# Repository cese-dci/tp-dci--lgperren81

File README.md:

# tp-dci--lgperren81
tp-dci--lgperren81 created by GitHub Classroom
Carpeta que contiene el TP Final de la materia "Diseño de Circuitos Impresos".
CESE 9° Cohorte - 2019

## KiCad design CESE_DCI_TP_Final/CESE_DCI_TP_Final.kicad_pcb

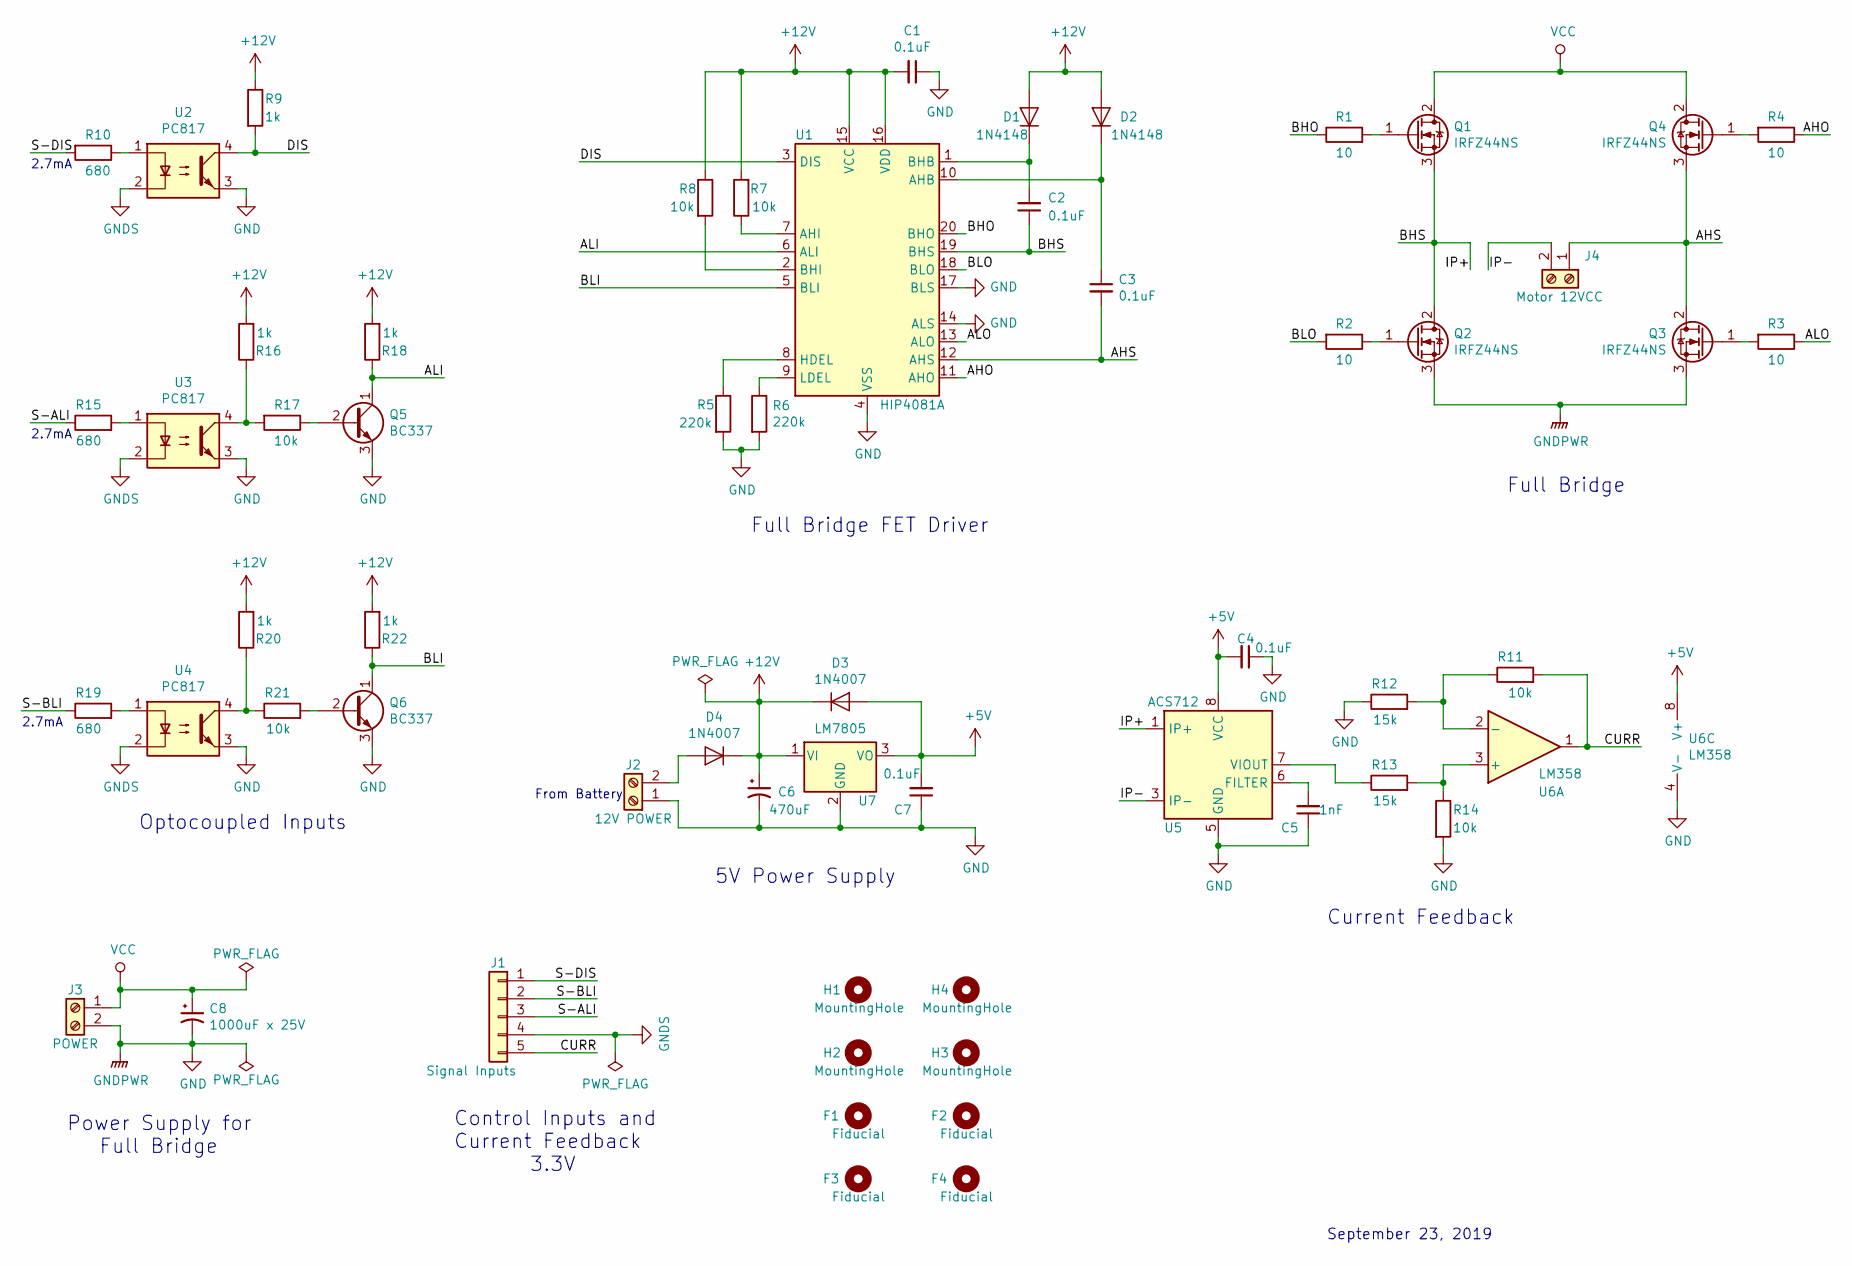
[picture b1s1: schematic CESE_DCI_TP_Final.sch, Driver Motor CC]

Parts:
C1, C2, C3, C4, C7: 0.1uF; C_1206_3216Metric_Pad1.42x1.75mm_HandSolder; Digi-Key Number 399-7357-2-ND
C5: 1nF; C_1206_3216Metric_Pad1.42x1.75mm_HandSolder; Digi-Key Number 399-17173-2-ND
C6: 470uF; CP_Radial_D10.0mm_P5.00mm; Digi-Key Number P10386TB-ND
C8: 1000uF x 25V; CP_Radial_D16.0mm_P7.50mm; Digi-Key Number 493-14604-3-ND
D1, D2: 1N4148; D_DO-35_SOD27_P7.62mm_Horizontal; Digi-Key Number 1N4148FS-ND
D3, D4: 1N4007; D_DO-41_SOD81_P10.16mm_Horizontal; Digi-Key Number 1N4007FSCT-ND
F1, F2, F3, F4: Fiducial; Fiducial_0.5mm_Dia_1mm_Outer
H1, H2, H3, H4: MountingHole; MountingHole_2.7mm_M2.5
J1: Signal Inputs; PinHeader_1x05_P2.54mm_Vertical; Digi-Key Number 732-5318-ND
J2: 12V POWER; TerminalBlock_bornier-2_P5.08mm; Digi-Key Number A113320-ND
J3: POWER; TerminalBlock_bornier-2_P5.08mm; Digi-Key Number A113320-ND
J4: Motor 12VCC; TerminalBlock_bornier-2_P5.08mm; Digi-Key Number A113320-ND
Q1, Q2, Q3, Q4: IRFZ44NS; TO-263-2; Digi-Key Number IRFZ44NSTRLPBFTR-ND
Q5, Q6: BC337; TO-92_Inline; Digi-Key Number BC33725TFRTR-ND
R1, R2, R3, R4: 10; R_1206_3216Metric_Pad1.42x1.75mm_HandSolder; Digi-Key Number CRM1206-FX-10R0ELFCT-ND
R5, R6: 220k; R_1206_3216Metric_Pad1.42x1.75mm_HandSolder; Digi-Key Number A130566TR-ND
R7, R8, R11, R14, R17, R21: 10k; R_1206_3216Metric_Pad1.42x1.75mm_HandSolder; Digi-Key Number 311-10KERTR-ND
R9, R16, R20, R22: 1k; R_1206_3216Metric_Pad1.42x1.75mm_HandSolder; Digi-Key Number CR1206-JW-102ELFTR-ND
R10, R15, R19: 680; R_1206_3216Metric_Pad1.42x1.75mm_HandSolder; Digi-Key Number 311-680FRCT-ND
R12, R13: 15k; R_1206_3216Metric_Pad1.42x1.75mm_HandSolder; Digi-Key Number A129824TR-ND
R18: 1k; R_1206_3216Metric_Pad1.42x1.75mm_HandSolder
U1: HIP4081A; DIP-20_W7.62mm_Socket; Digi-Key Number HIP4081AIPZ-ND
U2, U3, U4: PC817; DIP-4_W7.62mm; Digi-Key Number EL817-ND
U5: ACS712; SOIC-8_3.9x4.9mm_P1.27mm; Digi-Key Number 620-1190-2-ND
U6: LM358; SOIC-8-1EP_3.9x4.9mm_P1.27mm_EP2.35x2.35mm; Digi-Key Number 497-1591-2-ND
U7: LM7805; TO-220-3_Vertical; Digi-Key Number 296-47192-ND

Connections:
+5V: C4.2, C7.2, D3.2 (A), U5.8 (VCC), U6.8 (V+), U7.3 (VO)
+12V: C1.2, C6.1, D1.2 (A), D2.2 (A), D3.1 (K), D4.1 (K), R7.2, R8.1, R9.1, R16.2, R18.2, R20.2, R22.2, U1.15 (VCC), U1.16 (VDD), U7.1 (VI)
/AHO: R4.1, U1.11 (AHO)
/AHS: C3.2, J4.1, Q3.2 (D), Q4.3 (S), U1.12 (AHS)
/ALI: Q5.1 (C), R18.1, U1.6 (ALI)
/ALO: R3.1, U1.13 (ALO)
/BHO: R1.1, U1.20 (BHO)
/BHS: C2.1, Q1.3 (S), Q2.2 (D), U1.19 (BHS), U5.1 (IP+), U5.2 (IP+)
/BLI: Q6.1 (C), R22.1, U1.5 (BLI)
/BLO: R2.2, U1.18 (BLO)
/CURR: J1.5, R11.2, U6.1
/DIS: R9.2, U1.3 (DIS), U2.4
/IP-: J4.2, U5.3 (IP-), U5.4 (IP-)
/S-ALI: J1.3, R15.1
/S-BLI: J1.2, R19.1
/S-DIS: J1.1, R10.2
GND: C1.1, C4.1, C5.1, C6.2, C7.1, C8.2, J2.1, J3.2, Q2.3 (S), Q3.3 (S), Q5.3 (E), Q6.3 (E), R5.2, R6.2, R12.1, R14.2, U1.4 (VSS), U1.14 (ALS), U1.17 (BLS), U2.3, U3.3, U4.3, U5.5 (GND), U6.4 (V-), U7.2 (GND)
GNDS: J1.4, U2.2, U3.2, U4.2
unnamed: C2.2, D1.1 (K), U1.1 (BHB)
unnamed: C3.1, D2.1 (K), U1.10 (AHB)
unnamed: C5.2, U5.6 (FILTER)
unnamed: D4.2 (A), J2.2
unnamed: Q1.1 (G), R1.2
unnamed: Q2.1 (G), R2.1
unnamed: Q3.1 (G), R3.2
unnamed: Q4.1 (G), R4.2
unnamed: Q5.2 (B), R17.1
unnamed: Q6.2 (B), R21.2
unnamed: R5.1, U1.8 (HDEL)
unnamed: R6.1, U1.9 (LDEL)
unnamed: R7.1, U1.7 (AHI)
unnamed: R8.2, U1.2 (BHI)
unnamed: R10.1, U2.1
unnamed: R11.1, R12.2, U6.2 (-)
unnamed: R13.1, U5.7 (VIOUT)
unnamed: R13.2, R14.1, U6.3 (+)
unnamed: R15.2, U3.1
unnamed: R16.1, R17.2, U3.4
unnamed: R19.2, U4.1
unnamed: R20.1, R21.1, U4.4
VCC: C8.1, J3.1, Q1.2 (D), Q4.2 (D)

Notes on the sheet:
Control Inputs and Current Feedback 3.3V
From Battery
2.7mA
September 23, 2019
Current Feedback
Full Bridge
Full Bridge FET Driver
5V Power Supply
Optocoupled Inputs
Power Supply for Full Bridge

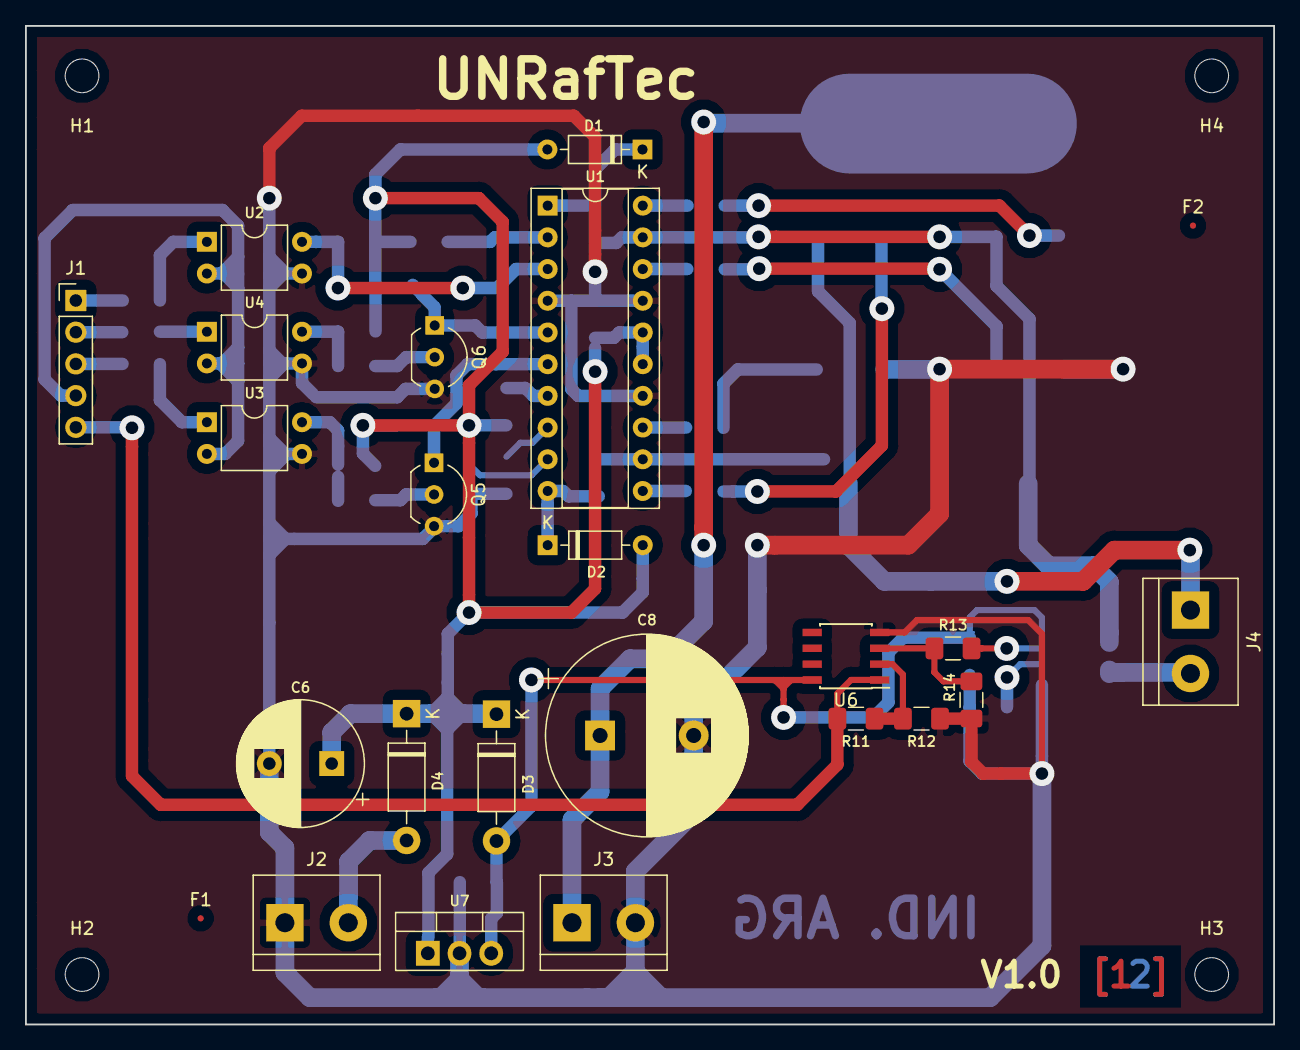
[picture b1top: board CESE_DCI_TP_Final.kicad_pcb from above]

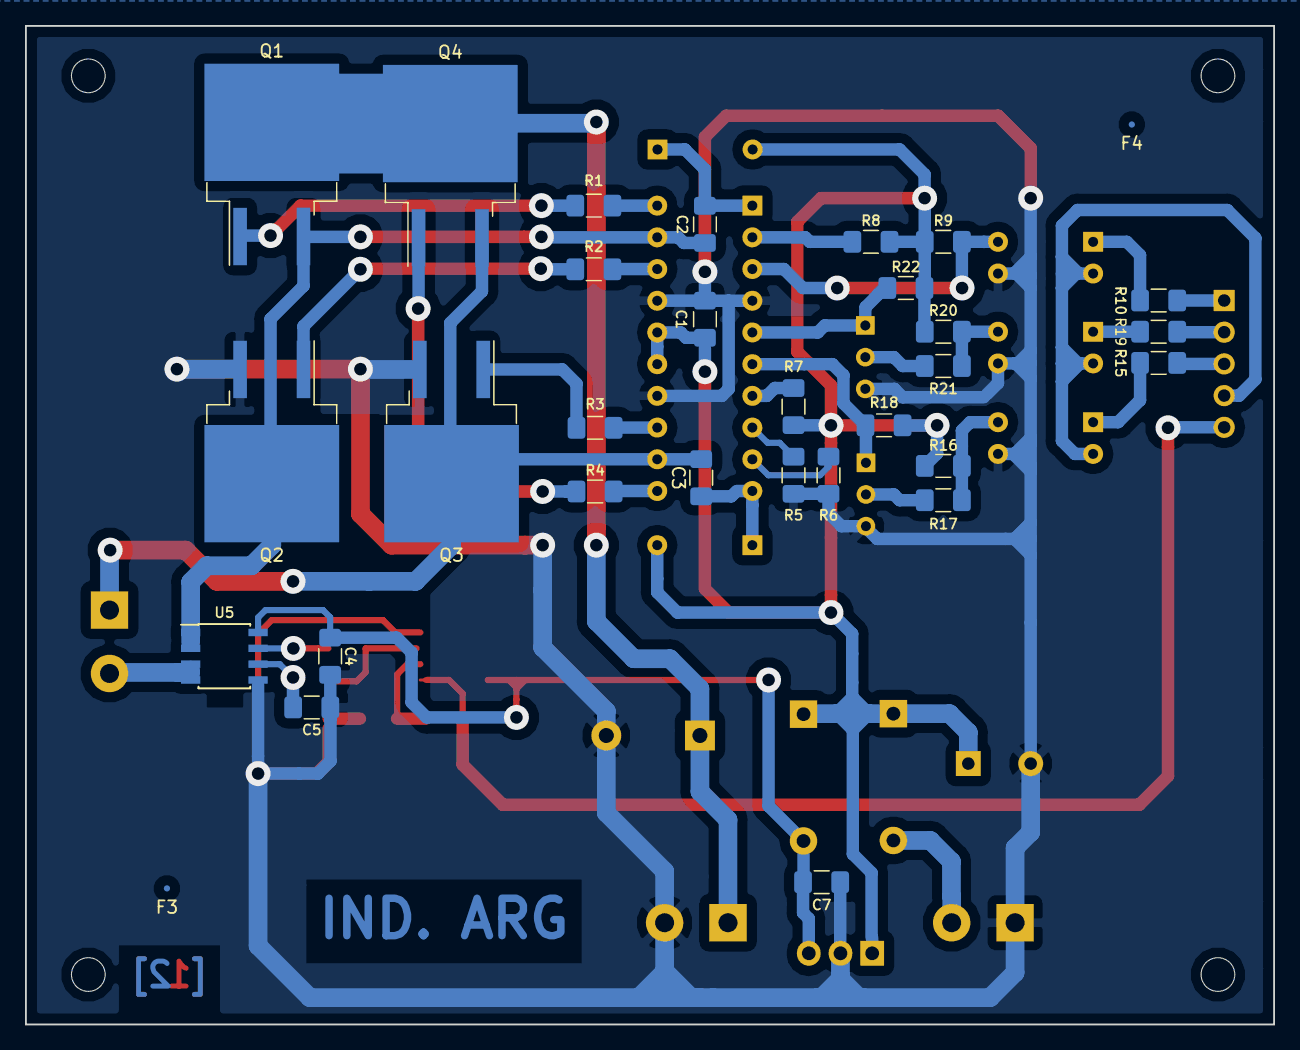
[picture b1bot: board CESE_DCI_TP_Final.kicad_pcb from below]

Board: 2 copper layers, 100.0 x 80.0 mm, 59 parts (31 on the bottom side), 41 nets.

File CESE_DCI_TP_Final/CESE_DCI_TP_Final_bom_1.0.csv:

Component,Description,Part,References,Value,Footprint,Quantity Per PCB,Datasheet
1,"Unpolarized capacitor, small symbol",C_Small,C1 C2 C3 C4 C7,0.1uF,C_1206_3216Metric_Pad1.42x1.75mm_HandSolder,5,~
2,"Polarized capacitor, small US symbol",CP1_Small,C8,1000uF x 25V,CP_Radial_D16.0mm_P7.50mm,1,~
3,"Unpolarized capacitor, small symbol",C_Small,C5,1nF,C_1206_3216Metric_Pad1.42x1.75mm_HandSolder,1,~
4,"Polarized capacitor, small US symbol",CP1_Small,C6,470uF,CP_Radial_D10.0mm_P5.00mm,1,~
5,"1000V 1A General Purpose Rectifier Diode, DO-41",1N4007,D3 D4,1N4007,D_DO-41_SOD81_P10.16mm_Horizontal,2,http://www.vishay.com/docs/88503/1n4001.pdf
6,"100V 0.15A standard switching diode, DO-35",1N4148,D1 D2,1N4148,D_DO-35_SOD27_P7.62mm_Horizontal,2,http://www.nxp.com/documents/data_sheet/1N4148_1N4448.pdf
7,"Generic screw terminal, single row, 01x02, script generated (kicad-library-utils/schlib/autogen/connector/)",Screw_Terminal_01x02,J2 J3,12V POWER,TerminalBlock_bornier-2_P5.08mm,2,~
8,"Generic connector, single row, 01x05, script generated (kicad-library-utils/schlib/autogen/connector/)",Conn_01x05,J1,Signal Inputs,PinHeader_1x05_P2.54mm_Vertical,1,~
9,DC Motor,Motor_DC,M1,Motor 12V CC,TerminalBlock_bornier-2_P5.08mm,1,~
10,"0.8A Ic, 45V Vce, NPN Transistor, TO-92",BC337,Q5 Q6,BC337,TO-92_Inline,2,http://www.nxp.com/documents/data_sheet/BC817_BC817W_BC337.pdf
11,"47A Id, 55V Vds, Single N-Channel HEXFET Power MOSFET, 22mOhm Ron, TO-220AB",IRLZ44N,Q1 Q2 Q3 Q4,IRFZ44NS,TO-263-2,4,http://www.irf.com/product-info/datasheets/data/irlz44n.pdf
12,Resistor,R,R1 R2 R3 R4,10,R_1206_3216Metric_Pad1.42x1.75mm_HandSolder,4,~
13,Resistor,R,R7 R8 R11 R14 R17 R21,10k,R_1206_3216Metric_Pad1.42x1.75mm_HandSolder,6,~
14,Resistor,R,R12 R13,15k,R_1206_3216Metric_Pad1.42x1.75mm_HandSolder,2,~
15,Resistor,R,R9 R16 R18 R20 R22,1k,R_1206_3216Metric_Pad1.42x1.75mm_HandSolder,5,~
16,Resistor,R,R5 R6,220k,R_1206_3216Metric_Pad1.42x1.75mm_HandSolder,2,~
17,Resistor,R,R10 R15 R19,680,R_1206_3216Metric_Pad1.42x1.75mm_HandSolder,3,~
18,"±20A Bidirectional Hall-Effect Current Sensor, +5.0V supply, 100mV/A, SOIC-8",ACS712xLCTR-20A,U5,ACS712,SOIC-8_3.9x4.9mm_P1.27mm,1,http://www.allegromicro.com/~/media/Files/Datasheets/ACS712-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
19,"High Frequency Full Bridge FET Driver, 2.5A, 80V, DIP-20/SOIC-20",HIP4081A,U1,HIP4081A,DIP-20_W7.62mm_Socket,1,http://www.intersil.com/content/dam/Intersil/documents/hip4/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
20,"Low-Power, Dual Operational Amplifiers, DIP-8/SOIC-8/TO-99-8",LM358,U6,LM358,SOIC-8-1EP_3.9x4.9mm_P1.27mm_EP2.35x2.35mm,1,http://www.ti.com/lit/ds/symlink/lm2904-n.pdf
21,"Positive 1A 35V Linear Regulator, Fixed Output 5V, TO-220",LM7805_TO220,U7,LM7805,TO-220-3_Vertical,1,http://www.fairchildsemi.com/ds/LM/LM7805.pdf
22,"DC Optocoupler, Vce 35V, CTR 50-300%, DIP4",PC817,U2 U3 U4,PC817,DIP-4_W7.62mm,3,http://www.soselectronic.cz/a_info/resource/d/pc817.pdf





Component Groups:,22
Component Count:,51
Fitted Components:,51
Number of PCBs:,1
Total components:,51
Schematic Version:,1.0
Schematic Date:,
PCB Variant:,[u'default']
BoM Date:,vie 01 nov 2019 20:16:39 -03
Schematic Source:,/home/lgperren/Documentos/DCI/CESE_DCI_TP_Final/CESE_DCI_TP_Final.sch
KiCad Version:,Eeschema 5.0.2-bee76a0~70~ubuntu18.04.1

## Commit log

2019-09-23 TP Final DCI
2019-09-25 Se actualizo el esquematico
2019-09-26 Se realizaron correcciones en el .sch
2019-09-28 Se corrijen errores ERC
2019-11-02 Se finaliza PCB + 3D View + BOM
2019-11-13 Se realizan correcciones
